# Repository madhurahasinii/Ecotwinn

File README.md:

# EcoTwin — Industrial Waste Accountability System

## Overview

EcoTwin is a proposed hardware and software system for improving the traceability, monitoring, and accountability of industrial liquid waste.

The project aims to help track waste quantity and basic quality parameters, record waste-handling activities, and improve transparency throughout the waste-management process.

## Problem Statement

Industrial liquid waste can pose environmental risks when it is inadequately treated, transported, or disposed of. Limited visibility into waste handling can make independent verification and accountability difficult.

EcoTwin proposes a system that combines physical measurement, digital recordkeeping, and waste-traceability features.

## Proposed System

1. **Waste collection tank:** Collects liquid waste at a designated factory or collection point.
2. **Weight measurement:** A load-cell-based system is proposed to estimate the quantity of collected waste.
3. **Quality monitoring:** Sensors such as pH sensors can be incorporated to measure selected waste characteristics.
4. **Electronics enclosure:** Houses the proposed measurement and processing electronics.
5. **Traceability dashboard:** A planned software interface for displaying measurements and waste-handling records.
6. **Waste reuse assessment:** A proposed feature to identify potential opportunities for reuse by suitable industrial processes.

## CAD Design

The Fusion 360 design includes a tank, lid, funnel, support platform, load cell representation, base, electronics enclosure, PCB representation, spacers, pole, and feet.

The CAD assembly represents the proposed physical arrangement of the system.

## Current Project Status

- Fusion 360 CAD assembly created.
- Major structural and enclosure components represented.
- Electronics enclosure and PCB representation included.
- Hardware integration and validation remain subject to further development.

> **Status note:** CAD representations do not establish that the corresponding hardware or software is operational. Sensor integration, calibration, data acquisition, dashboard connectivity, and waste-traceability functions must be validated separately.

## Future Work

- Integrate and calibrate the load cell.
- Integrate a suitable pH sensor and measurement circuit.
- Develop reliable data acquisition and storage.
- Build the waste-traceability dashboard.
- Add QR-based identification and handling records.
- Evaluate waste reuse opportunities using appropriate technical and regulatory criteria.
- Conduct controlled experiments and validate measurement accuracy.
- Evaluate enclosure sealing, material compatibility, and operational safety.

## Project Files

- `docs/CAD/ecotwin_final.f3z` — Fusion 360 assembly archive.
- `screenshots/` — CAD assembly screenshots, if included.
- `README.md` — Project overview and documentation.

## Disclaimer

This project is a design-stage prototype concept. Its measurements, traceability mechanisms, and environmental benefits require implementation and validation before real-world deployment.

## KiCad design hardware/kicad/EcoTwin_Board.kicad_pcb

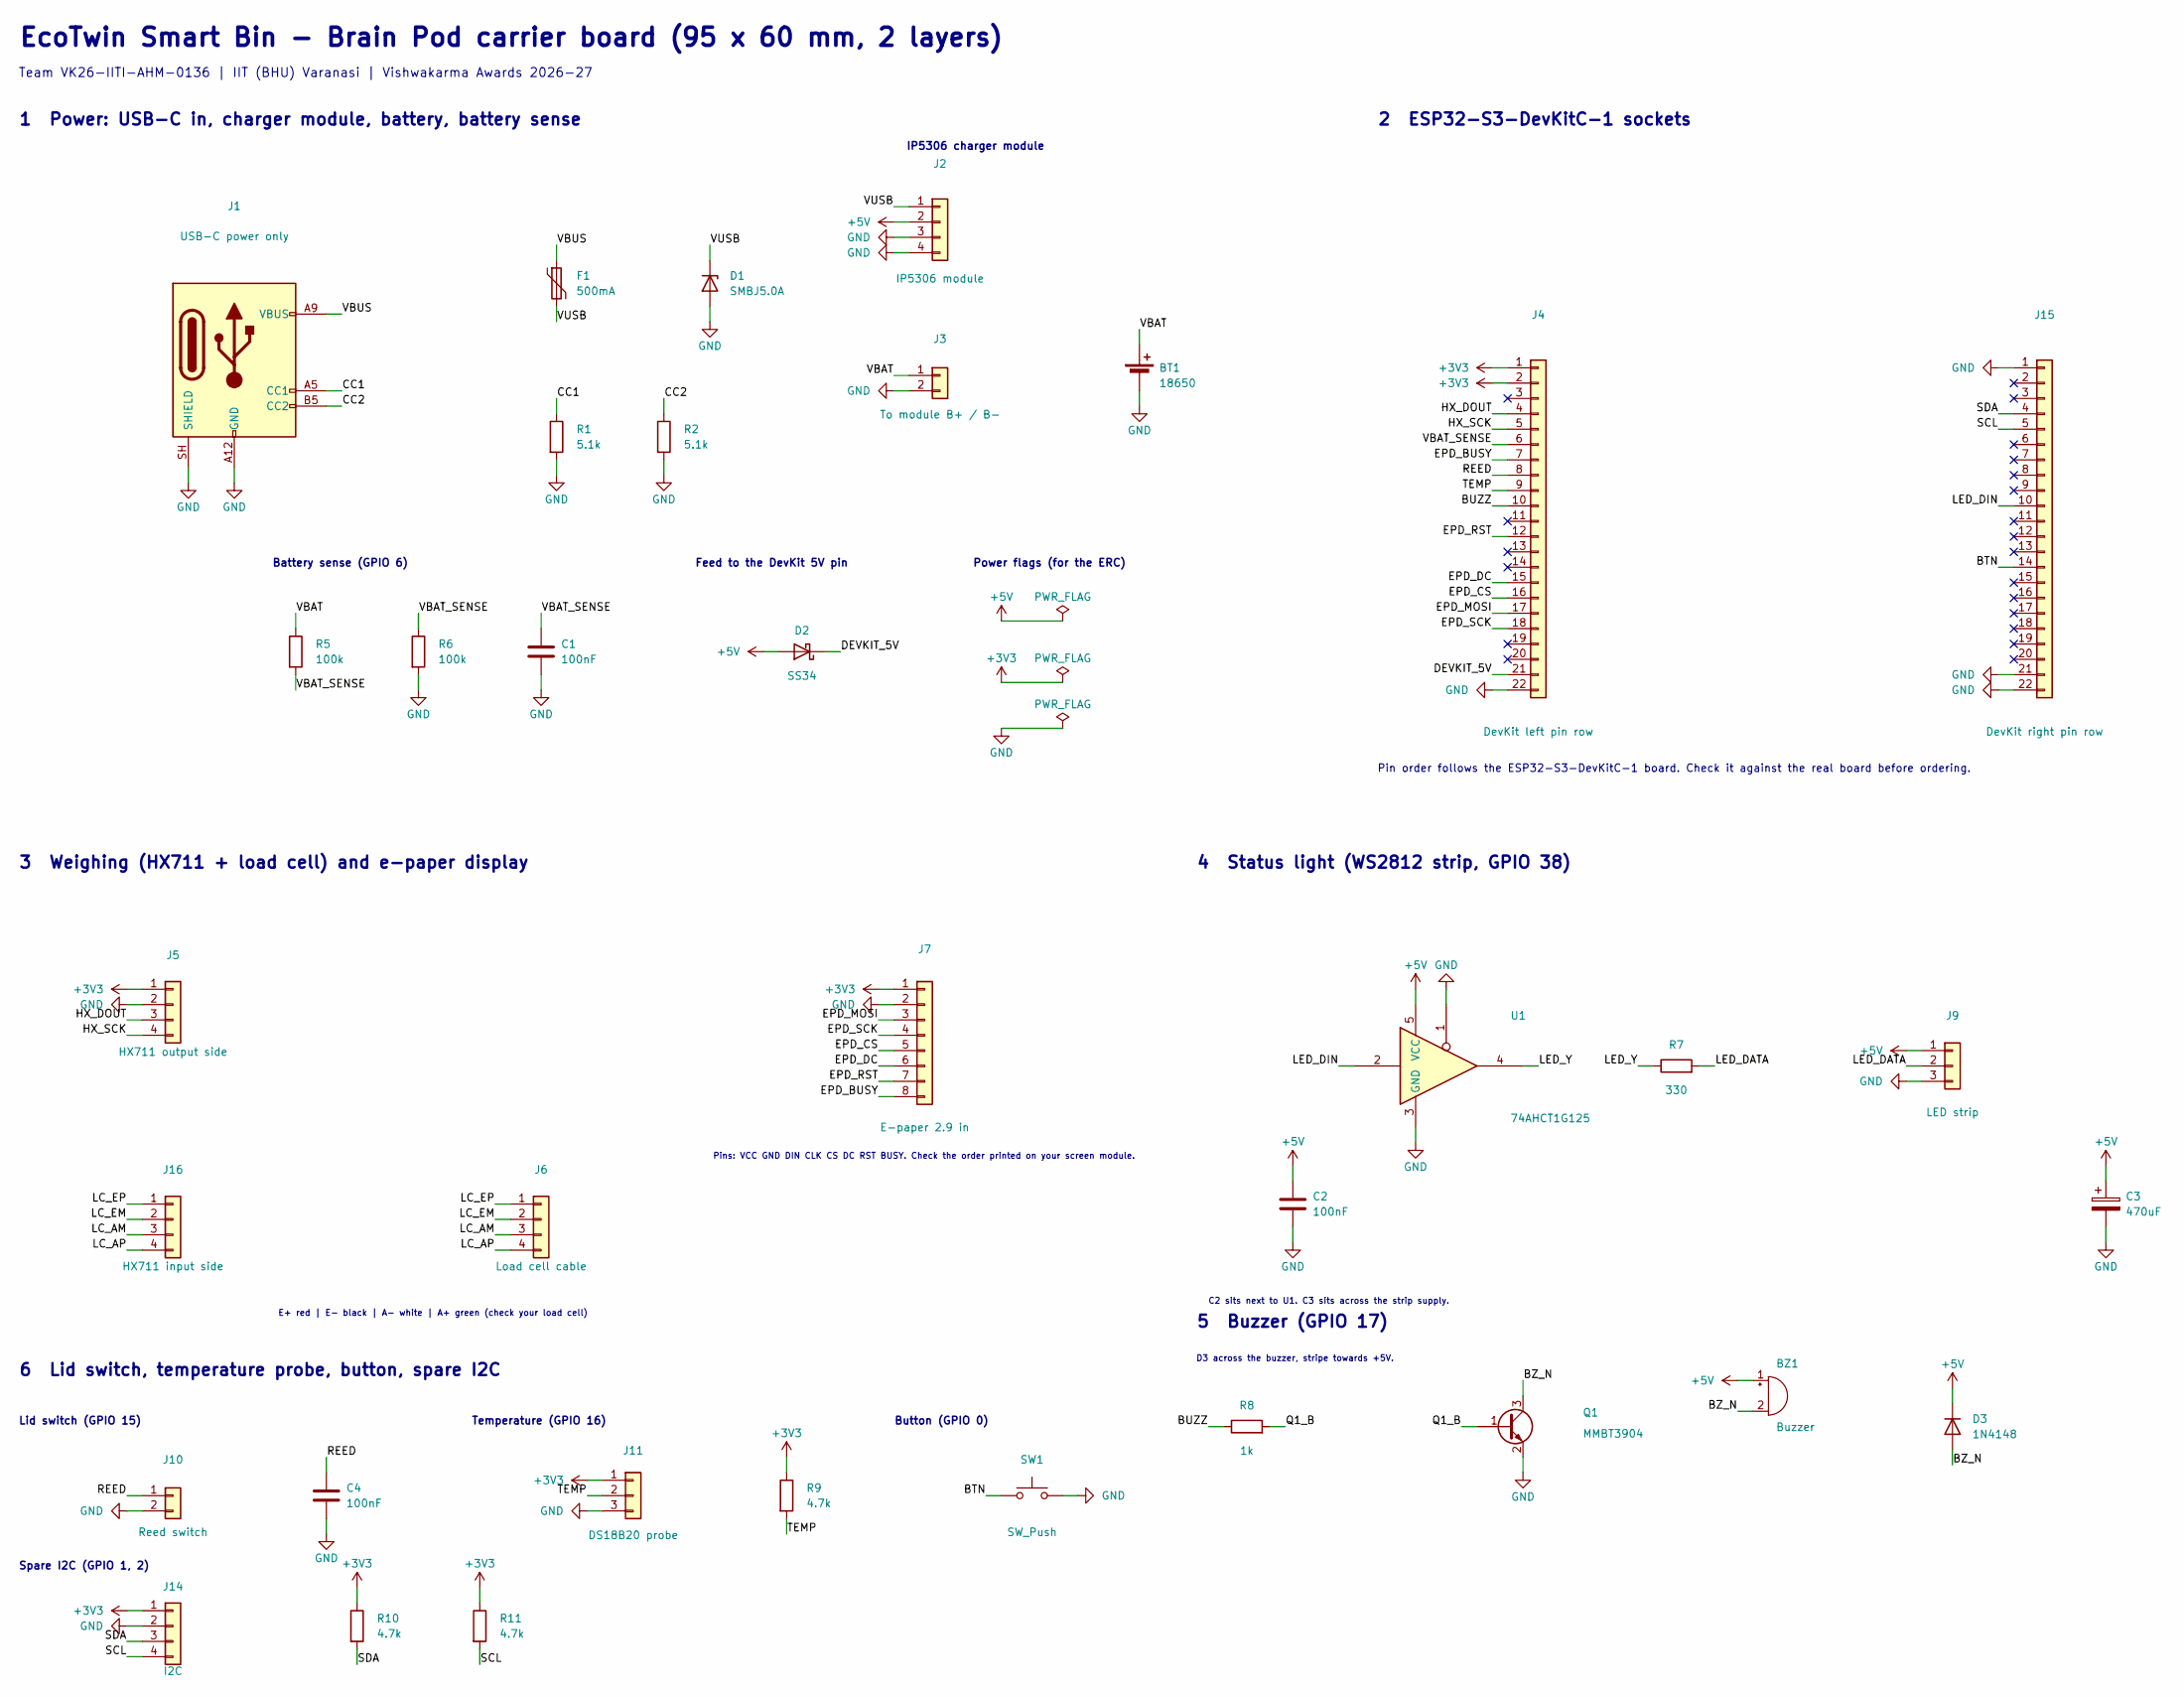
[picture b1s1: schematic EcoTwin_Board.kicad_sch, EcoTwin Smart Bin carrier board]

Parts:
BT1: 18650; BatteryHolder_Keystone_1042_1x18650
BZ1: Buzzer; Buzzer_12x9.5RM7.6
C1, C2, C4: 100nF; C_0805_2012Metric
C3: 470uF; CP_Radial_D8.0mm_P3.50mm
D1: SMBJ5.0A; D_SMB
D2: SS34; D_SMA
D3: 1N4148; D_SOD-123
F1: 500mA; Fuse_1206_3216Metric
J1: USB-C power only; USB_C_Receptacle_GCT_USB4125-xx-x_6P_TopMnt_Horizontal
J2: IP5306 module; PinHeader_1x04_P2.54mm_Vertical
J3: To module B+ / B-; JST_XH_B2B-XH-A_1x02_P2.50mm_Vertical
J4: DevKit left pin row; PinSocket_1x22_P2.54mm_Vertical
J5: HX711 output side; PinHeader_1x04_P2.54mm_Vertical
J6: Load cell cable; JST_XH_B4B-XH-A_1x04_P2.50mm_Vertical
J7: E-paper 2.9 in; PinHeader_1x08_P2.54mm_Vertical
J9: LED strip; JST_XH_B3B-XH-A_1x03_P2.50mm_Vertical
J10: Reed switch; JST_XH_B2B-XH-A_1x02_P2.50mm_Vertical
J11: DS18B20 probe; JST_XH_B3B-XH-A_1x03_P2.50mm_Vertical
J14: I2C; JST_XH_B4B-XH-A_1x04_P2.50mm_Vertical
J15: DevKit right pin row; PinSocket_1x22_P2.54mm_Vertical
J16: HX711 input side; PinHeader_1x04_P2.54mm_Vertical
Q1: MMBT3904; SOT-23
R1, R2: 5.1k; R_0805_2012Metric
R5, R6: 100k; R_0805_2012Metric
R7: 330; R_0805_2012Metric
R8: 1k; R_0805_2012Metric
R9, R10, R11: 4.7k; R_0805_2012Metric
SW1: SW_Push; SW_PUSH_6mm
U1: 74AHCT1G125; SOT-23-5

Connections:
+3V3: J4.1, J4.2, J5.1, J7.1, J11.1, J14.1, R9.1, R10.1, R11.1
+5V: BZ1.1 (+), C2.1, C3.1, D2.2 (A), D3.1 (K), J2.2, J9.1, U1.5 (VCC)
/BTN: J15.14, SW1.1
/BUZZ: J4.10, R8.1
/BZ_N: BZ1.2 (-), D3.2 (A), Q1.3 (C)
/CC1: J1.A5 (CC1), R1.1
/CC2: J1.B5 (CC2), R2.1
/DEVKIT_5V: D2.1 (K), J4.21
/EPD_BUSY: J4.7, J7.8
/EPD_CS: J4.16, J7.5
/EPD_DC: J4.15, J7.6
/EPD_MOSI: J4.17, J7.3
/EPD_RST: J4.12, J7.7
/EPD_SCK: J4.18, J7.4
/HX_DOUT: J4.4, J5.3
/HX_SCK: J4.5, J5.4
/LC_AM: J6.3, J16.3
/LC_AP: J6.4, J16.4
/LC_EM: J6.2, J16.2
/LC_EP: J6.1, J16.1
/LED_DATA: J9.2, R7.2
/LED_DIN: J15.10, U1.2
/LED_Y: R7.1, U1.4
/Q1_B: Q1.1 (B), R8.2
/REED: C4.1, J4.8, J10.1
/SCL: J14.4, J15.5, R11.2
/SDA: J14.3, J15.4, R10.2
/TEMP: J4.9, J11.2, R9.2
/VBAT: BT1.1 (+), J3.1, R5.1
/VBAT_SENSE: C1.1, J4.6, R5.2, R6.1
/VBUS: F1.1, J1.A9 (VBUS), J1.B9 (VBUS)
/VUSB: D1.1 (K), F1.2, J2.1
GND: BT1.2 (-), C1.2, C2.2, C3.2, C4.2, D1.2 (A), J1.A12 (GND), J1.B12 (GND), J1.SH (SHIELD), J2.3, J2.4, J3.2, J4.22, J5.2, J7.2, J9.3, J10.2, J11.3, J14.2, J15.1, J15.21, J15.22, Q1.2 (E), R1.2, R2.2, R6.2, SW1.2, U1.1, U1.3 (GND)

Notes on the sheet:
EcoTwin Smart Bin - Brain Pod carrier board (95 x 60 mm, 2 layers)
Team VK26-IITI-AHM-0136 | IIT (BHU) Varanasi | Vishwakarma Awards 2026-27
1 Power: USB-C in, charger module, battery, battery sense
IP5306 charger module
Battery sense (GPIO 6)
Feed to the DevKit 5V pin
Power flags (for the ERC)
2 ESP32-S3-DevKitC-1 sockets
Pin order follows the ESP32-S3-DevKitC-1 board. Check it against the real board before ordering.
3 Weighing (HX711 + load cell) and e-paper display
E+ red | E- black | A- white | A+ green (check your load cell)
Pins: VCC GND DIN CLK CS DC RST BUSY. Check the order printed on your screen module.
4 Status light (WS2812 strip, GPIO 38)
C2 sits next to U1. C3 sits across the strip supply.
5 Buzzer (GPIO 17)
D3 across the buzzer, stripe towards +5V.
6 Lid switch, temperature probe, button, spare I2C
Lid switch (GPIO 15)
Temperature (GPIO 16)
Button (GPIO 0)
Spare I2C (GPIO 1, 2)

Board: 2 copper layers, 39 parts (1 on the bottom side), 33 nets, no tracks yet.

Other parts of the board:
H1, H2, H3, H4: MountingHole_3.2mm_M3
